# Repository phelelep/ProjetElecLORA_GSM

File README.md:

# 🐝 Ruche Connectée – Passerelle LoRa ↔ GSM

Projet réalisé dans le cadre du **cours de Projet d'Électronique** à **Polytech Nice Sophia Antipolis**,  
encadré par **M. Christian Peter** (*Christian.PETER@univ-cotedazur.fr*).

**Groupe :**  
- CEBAN Daniel — [ceban.daniel@etu.univ-cotedazur.fr] 
- MIRRIONE Xavier  — [mirrione.xavier@etu.univ-cotedazur.fr]

---

## 🎯 Objectif du projet

Ce projet vise à concevoir une **ruche connectée** capable de :

- Collecter et transmettre à distance des données environnementales ;  
- Communiquer via une **passerelle LoRa ↔ GSM** ;  
- Intégrer des fonctions avancées comme **l’élimination des parasites par laser**.

Cette partie du projet se concentre sur **la communication à distance** des données.

---

## Dossiers :
- 📁 CompteRendu_Daniel
- 📁 CompteRendu_Xavier
- 📁 Partie_Electronique
- 📁 Partie_Informatique

---

## GLOSSAIRE :

- GSM (Global System for Mobile Communications) :
C'est un standard de communication mobile utilisé pour la téléphonie cellulaire et la transmission de données. Il permet l’envoi de messages SMS, les appels et la connexion à Internet via GPRS/EDGE/3G/4G. Le GSM est largement utilisé pour les dispositifs IoT nécessitant une connectivité dans des environnements sans Wi-Fi.

- LoRa (Long Range) :
C'est une technologie de communication sans fil à longue portée et à faible consommation d'énergie, utilisée pour connecter des dispositifs IoT aux réseaux LPWAN (Low Power Wide Area Network). LoRa permet de transmettre de petits paquets de données sur de longues distances (jusqu'à 15 km en zones rurales) avec une consommation d’énergie minimale.

- ESP32 :
C'est un microcontrôleur développé par Espressif, intégrant Wi-Fi et Bluetooth, ainsi que plusieurs broches GPIO pour les capteurs et modules externes. Il est largement utilisé dans les projets IoT grâce à sa connectivité, sa puissance et son faible coût.
Il va nous permetre de récuperer les information des LoRa et les envoier vers le module GSM pour ensuite transmettre les information au utilisateur.

- SIM7000 :
C'est un module de communication GSM/GPRS/NB-IoT/LTE Cat-M1 développé par Simcom. Il permet aux dispositifs IoT d'envoyer et de recevoir des données via les réseaux mobiles, en prenant en charge les connexions basse consommation, idéales pour les capteurs distants et les applications de surveillance.

---

## 🧩 Technologies utilisées

- **ESP32** – Microcontrôleur principal du système.  
- **SIM7000G** – Module GSM / NB-IoT / LTE pour la communication mobile.  
- **LoRa** – Communication longue portée et faible consommation.  
- **TinyGSM** – Bibliothèque facilitant la communication série avec le SIM7000G.

---

## ⚙️ Fonctionnement général

1. Initialisation et configuration du modem GSM (SIM7000G).  
2. Connexion au réseau mobile via **APN SFR** (`sl2sfr`).  
3. Transmission ou test d’envoi de données / SMS.  
4. Préparation à l’intégration de la communication **LoRa** pour la collecte distante.  

---

## Etapes du projet 

### 🚧 Etape 1:
- Analyse du projet existant et definier les tacher pour continuer le projet. Repartition des taches dans le groupe 

---

## 💡 Référence du projet précédent

Ce projet est basé sur le travail de la promotion précédente :  
**Oumar Sadjo Barry** & **Mor Dieng** – *RucherLoRa*  
- Guilherme Ventapane Rodrigues — [guilherme@ventapane.eu](mailto:guilherme@ventapane.eu)  
- Jarod Lecoeuvre — [jarod.lecoeuvre@etu.univ-cotedazur.fr](mailto:jarod.lecoeuvre@etu.univ-cotedazur.fr)

---

## 🧠 Encadrant

**M. Christian Peter**  
_Enseignant – Département Électronique & Informatique Industrielle_  
[Christian.PETER@univ-cotedazur.fr](mailto:Christian.PETER@univ-cotedazur.fr)

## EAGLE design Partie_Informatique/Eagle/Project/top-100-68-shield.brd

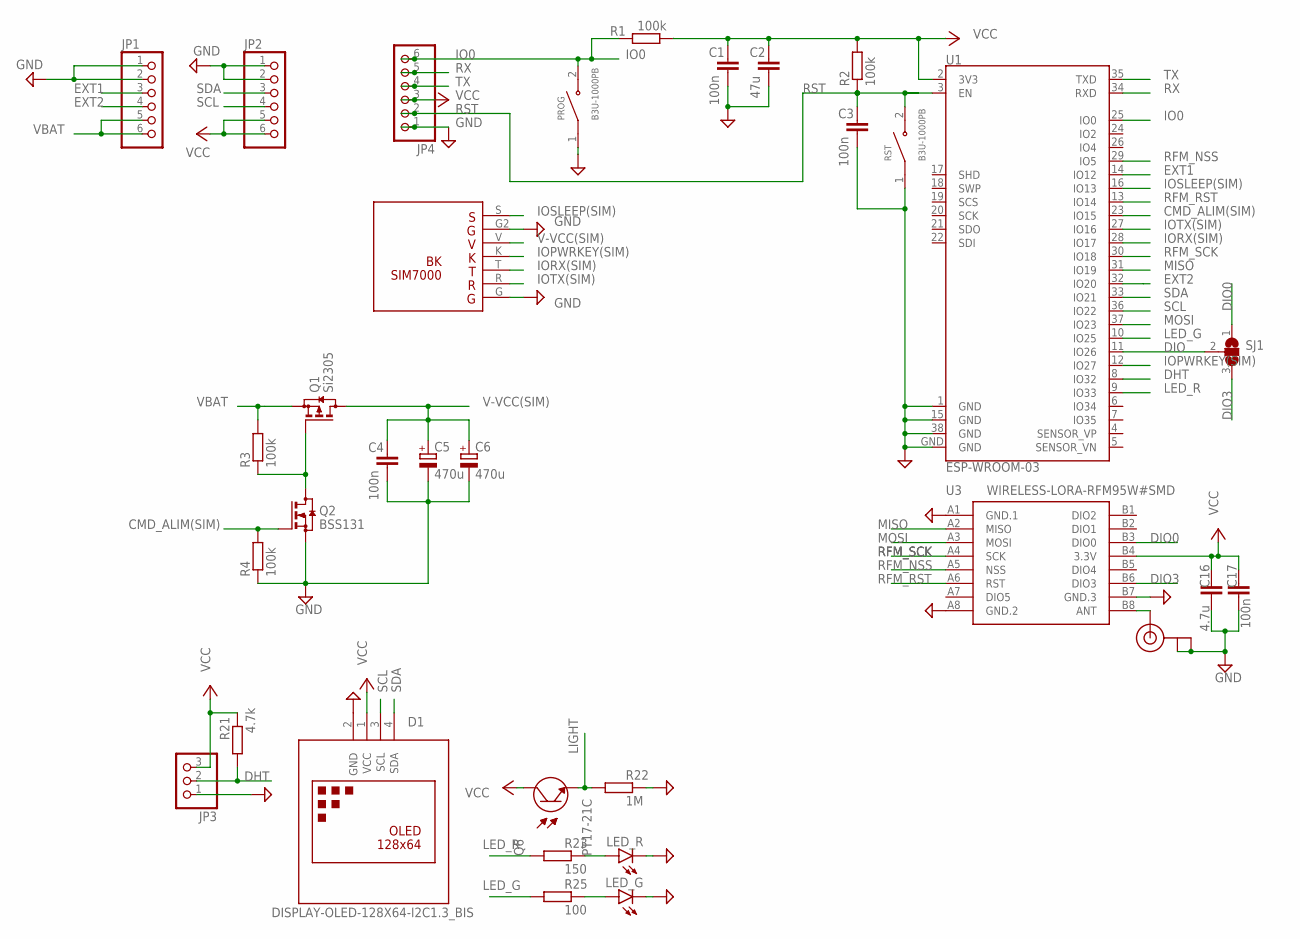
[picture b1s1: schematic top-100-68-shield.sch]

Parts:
C1, C3, C4, C17: 100n; C1206
C2: 47u; C0805
C5, C6: 470u; CT7343
C16: 4.7u; C1210
D1: DISPLAY-OLED-128X64-I2C1.3_BIS; DISPLAY-OLED-128X64-1.3-I2C_BIS
J1: U.FL
JP1, JP2, JP4: PINHD-1X6S; 1X06S
JP3: PINHD-1X3; 1X03
LED_G: LEDSMT1206; 1206
LED_R: LEDSMT1206; 1206
PROG: B3U-1000PB; SW_B3U-1000PB
Q1: Si2305; SOT23
Q2: BSS131; SOT23
Q6: PT17-21C; 0805
R1, R2, R3, R4: 100k; R1206
R21: 4.7k; R1206
R22: 1M; R1206
R23: 150; R1206
R25: 100; R1206
RST: B3U-1000PB; SW_B3U-1000PB
SJ1: SJ2W; SJ_2
U1: ESP-WROOM-03
U2: BK7000-V2; SIM7000-BK
U3: WIRELESS-LORA-RFM95W#SMD

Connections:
ANT: J1.3 (SIGNAL), U3.B8 (ANT)
CMD_ALIM(SIM): Q2.1 (G), R4.2, U1.23 (IO15)
DHT: JP3.2, R21.1, U1.8 (IO32)
DIO: SJ1.2, U1.11 (IO26)
DIO0: SJ1.1, U3.B3 (DIO0)
DIO3: SJ1.3, U3.B6 (DIO3)
EXT1: JP1.3, U1.14 (IO12)
EXT2: JP1.4, U1.32 (IO20)
GND: C1.2, C2.2, C3.2, C4.2, C5.-, C6.-, C16.2, C17.2, D1.2 (GND), J1.1 (GND), J1.2 (GND), JP1.1, JP1.2, JP2.1, JP2.2, JP3.1, JP4.1, LED_G.C, LED_R.C, PROG.1, Q2.2 (S), R4.1, R22.2, RST.1, U1.1 (GND), U1.15 (GND), U1.38 (GND), U1.GND, U2.G, U2.G2, U3.A1 (GND.1), U3.A8 (GND.2), U3.B7 (GND.3)
IO0: JP4.6, PROG.2, R1.2, U1.25 (IO0)
IOPWRKEY(SIM): U1.12 (IO27), U2.K
IORX(SIM): U1.28 (IO17), U2.T
IOSLEEP(SIM): U1.16 (IO13), U2.S
IOTX(SIM): U1.27 (IO16), U2.R
LED_G: R25.1, U1.10 (IO25)
LED_R: R23.1, U1.9 (IO33)
LIGHT: Q6.1 (E), R22.1
MISO: U1.31 (IO19), U3.A2 (MISO)
MOSI: U1.37 (IO23), U3.A3 (MOSI)
unnamed: Q1.1 (G), Q2.3 (D), R3.1
unnamed: LED_R.A, R23.2
unnamed: LED_G.A, R25.2
RFM_NSS: U1.29 (IO5), U3.A5 (NSS)
RFM_RST: U1.13 (IO14), U3.A6 (RST)
RFM_SCK: U1.30 (IO18), U3.A4 (SCK)
RST: C3.1, JP4.2, R2.1, RST.2, U1.3 (EN)
RX: JP4.5, U1.34 (RXD)
SCL: D1.3 (SCL), JP2.4, U1.36 (IO22)
SDA: D1.4 (SDA), JP2.3, U1.33 (IO21)
TX: JP4.4, U1.35 (TXD)
V-VCC(SIM): C4.1, C5.+, C6.+, Q1.3 (D), U2.V
VBAT: JP1.5, JP1.6, Q1.2 (S), R3.2
VCC: C1.1, C2.1, C16.1, C17.1, D1.1 (VCC), JP2.5, JP2.6, JP3.3, JP4.3, Q6.2 (C), R1.1, R2.2, R21.2, U1.2 (3V3), U3.B4 (3.3V)

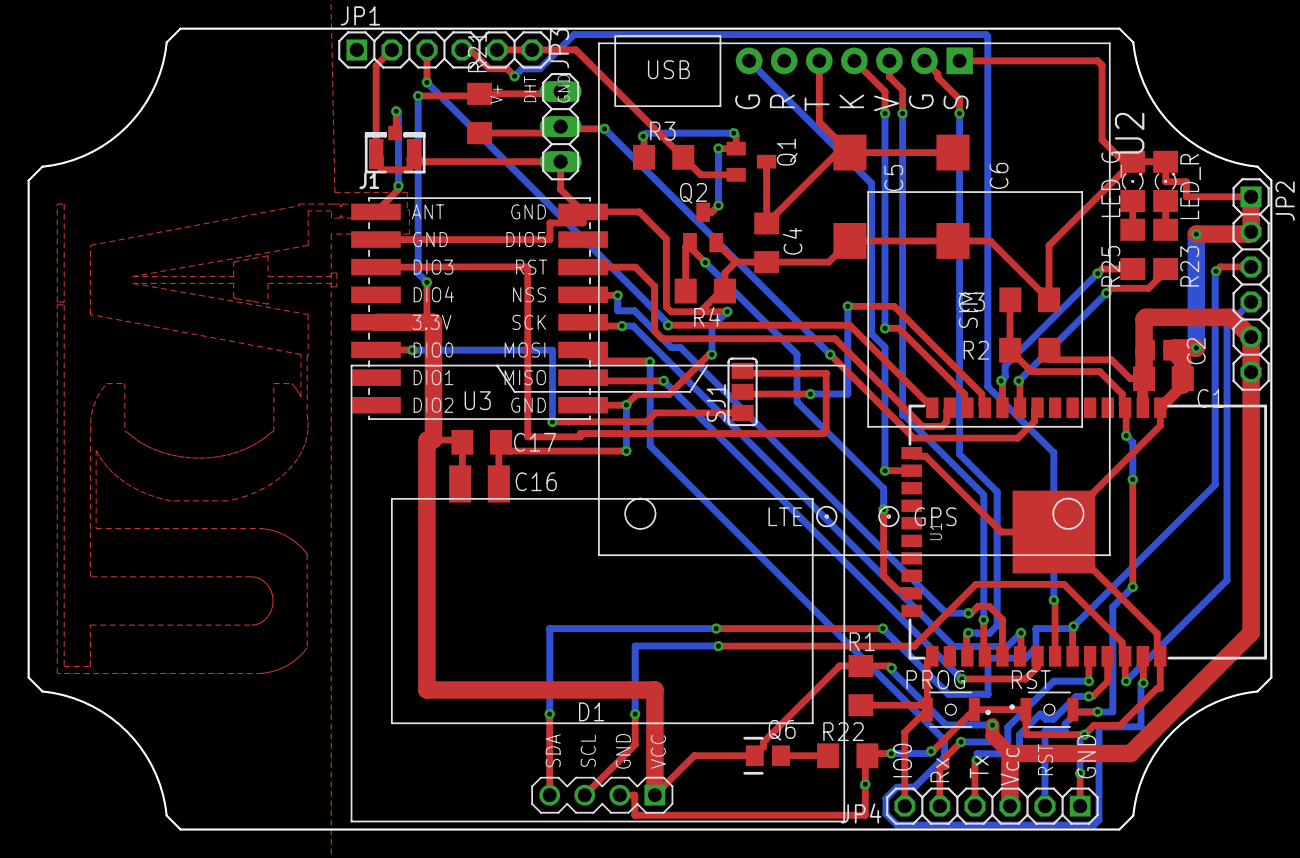
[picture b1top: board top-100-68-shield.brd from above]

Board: 2 copper layers, 90.0 x 58.0 mm, 33 parts (0 on the bottom side), 33 nets.

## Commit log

2025-10-08 Init Read Me
2025-10-08 Ajout de cahier de charge et rapport seance du 08
2025-10-23 Add Folder CR_XM
2025-10-23 Image schéma principe projet
2025-10-23 Ajout SchémaProjet
    Il a été rename puis déplacé dans le folder image
2025-10-23 AddPicture+Rapport23-10-25
2025-10-23 modifs
2025-10-23 AddDatasheetFolder
2025-10-23 modif
2025-10-23 Compte rendu 23_10
2025-10-23 push
2025-11-04 debut seance 3
2025-11-04 seance 04112025
2025-11-04 04-11-25_UPDATE
2025-11-12 seance du 11 novembre
2025-11-27 Seance 27 novembre
2025-11-28 seance6
2025-11-28 28-11-2025-RESOLVE_CONFLICT
2025-12-11 Mighty Push Pain
2025-12-11 11_12_2025
    Rédaction rapport et recherche ntenne 50 Ohm pin 9 LoRa et vérification via oscilloscope 3V3 et 5V du Serial adaptateur Board
2025-12-12 mighty push
2025-12-23 Seance7_Push
2025-12-23 Correctif Link Image
    le path des images n'étaient pas correctes
2026-01-20 they run the risk of carrying hate
2026-01-21 Seance 9
2026-02-03 OubliePush
    Lors de l'oral
2026-02-03 Seance10
    Eagle Sheet
2026-02-03 Seance10
2026-02-17 Seance 11
2026-02-17 Push-Seance11
    Avancement et explication Schematic Board sous EAGLE
2026-02-19 Seance 12
2026-03-05 PushSeance12-19_02
2026-03-05 Seance 13
2026-03-05 Seance13
2026-03-17 Seance14-15
2026-03-17 Seance 14
2026-04-03 Seance15
2026-04-10 Seance16
2026-04-10 Seance17-RoutagePCB
    RAS, c'est FINIS
2026-04-19 eco_conception
2026-04-22 corrige files
2026-04-22 compte_rendu
2026-04-24 Seance18
    Ajout dernière version du projet EAGLE.
2026-04-24 seance18
2026-05-05 Ajout PowerPoint et schematic final
2026-05-05 A FINIR !
2026-05-14 Rapport final

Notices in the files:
parts and their libraries:
diy-modules: Released under the Creative Commons Attribution 4.0 International License: http://creativecommons.org/licenses/by/4.0
